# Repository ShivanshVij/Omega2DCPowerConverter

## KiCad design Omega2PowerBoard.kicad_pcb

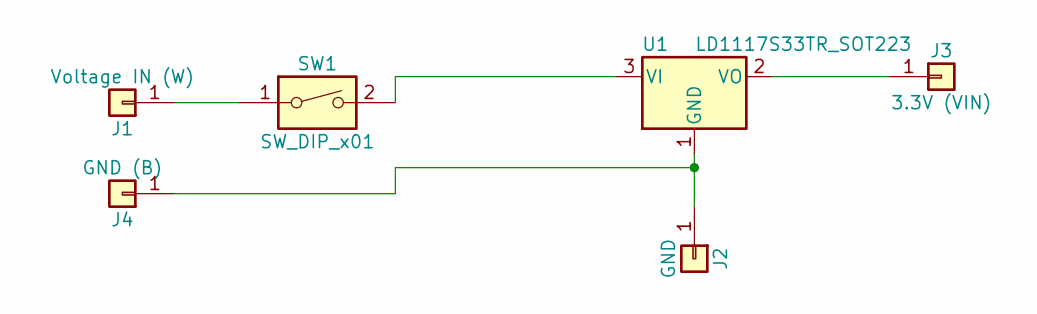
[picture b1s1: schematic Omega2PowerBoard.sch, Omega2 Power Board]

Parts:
J1: Voltage IN (W); SolderWirePad_single_1-2mmDrill
J2: GND; Socket_Strip_Straight_1x01_Pitch2.54mm
J3: 3.3V (VIN); Socket_Strip_Straight_1x01_Pitch2.54mm
J4: GND (B); SolderWirePad_single_1-2mmDrill
SW1: SW_DIP_x01; Socket_Strip_Straight_1x03_Pitch2.54mm
U1: LD1117S33TR_SOT223; Socket_Strip_Straight_1x03_Pitch2.54mm

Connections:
unnamed: J1.1, SW1.1
unnamed: J2.1, J4.1, U1.1 (GND)
unnamed: J3.1, U1.2 (VO)
unnamed: SW1.2, U1.3 (VI)

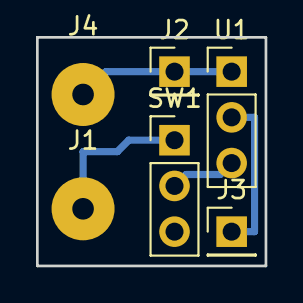
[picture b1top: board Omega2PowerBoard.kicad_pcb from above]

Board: 2 copper layers, 12.7 x 12.7 mm, 6 parts (0 on the bottom side), 4 nets.

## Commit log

2017-10-25 Added generated KiCAD Files
